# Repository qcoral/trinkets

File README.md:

# trinkets
Misc electronic trinkets &amp; designs I've made!

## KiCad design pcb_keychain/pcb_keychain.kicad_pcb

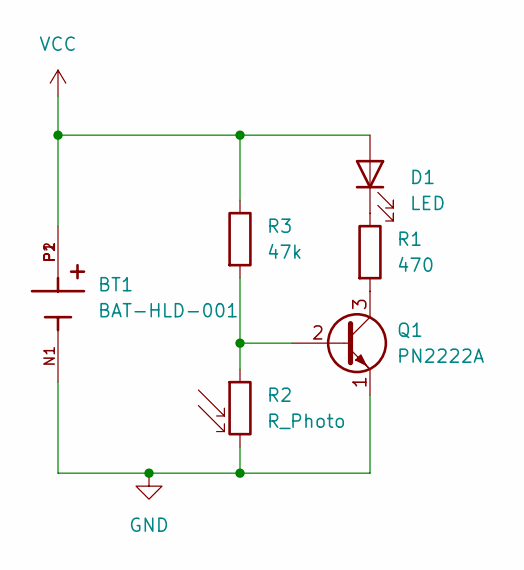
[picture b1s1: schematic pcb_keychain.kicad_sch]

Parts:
BT1: BAT-HLD-001; BAT_BAT-HLD-001; PARTREV C
D1: LED; LED_D8.0mm
Q1: PN2222A; TO-92_Inline
R1: 470; R_Axial_DIN0207_L6.3mm_D2.5mm_P10.16mm_Horizontal
R2: R_Photo; R_LDR_5.1x4.3mm_P3.4mm_Vertical
R3: 47k; R_Axial_DIN0207_L6.3mm_D2.5mm_P10.16mm_Horizontal

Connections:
GND: BT1.N1, Q1.1 (E), R2.2
unnamed: D1.1 (K), R1.1
unnamed: Q1.2 (B), R2.1, R3.2
unnamed: Q1.3 (C), R1.2
VCC: BT1.P1, BT1.P2, D1.2 (A), R3.1

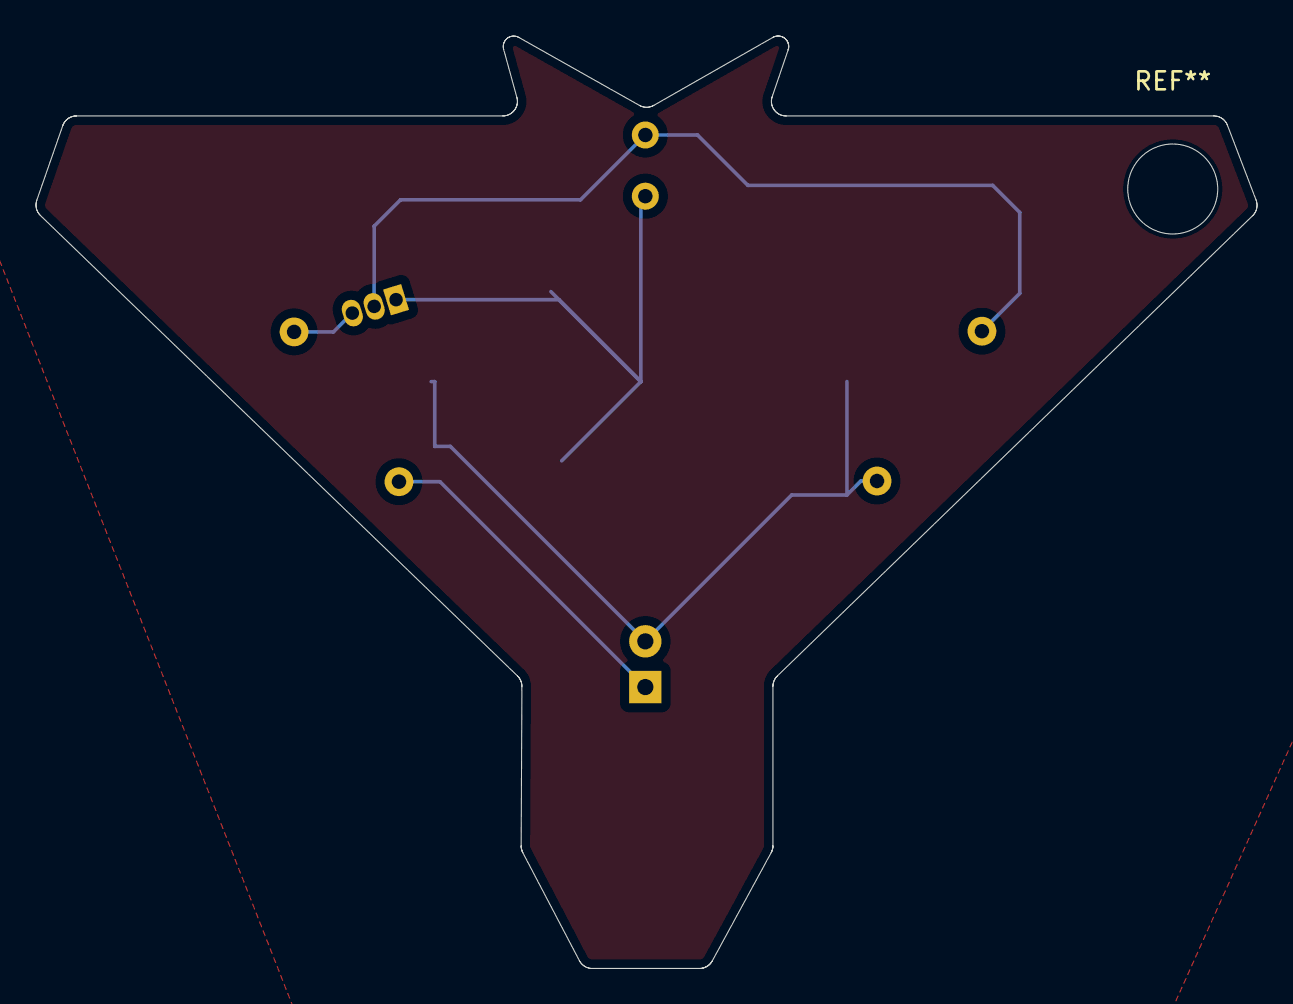
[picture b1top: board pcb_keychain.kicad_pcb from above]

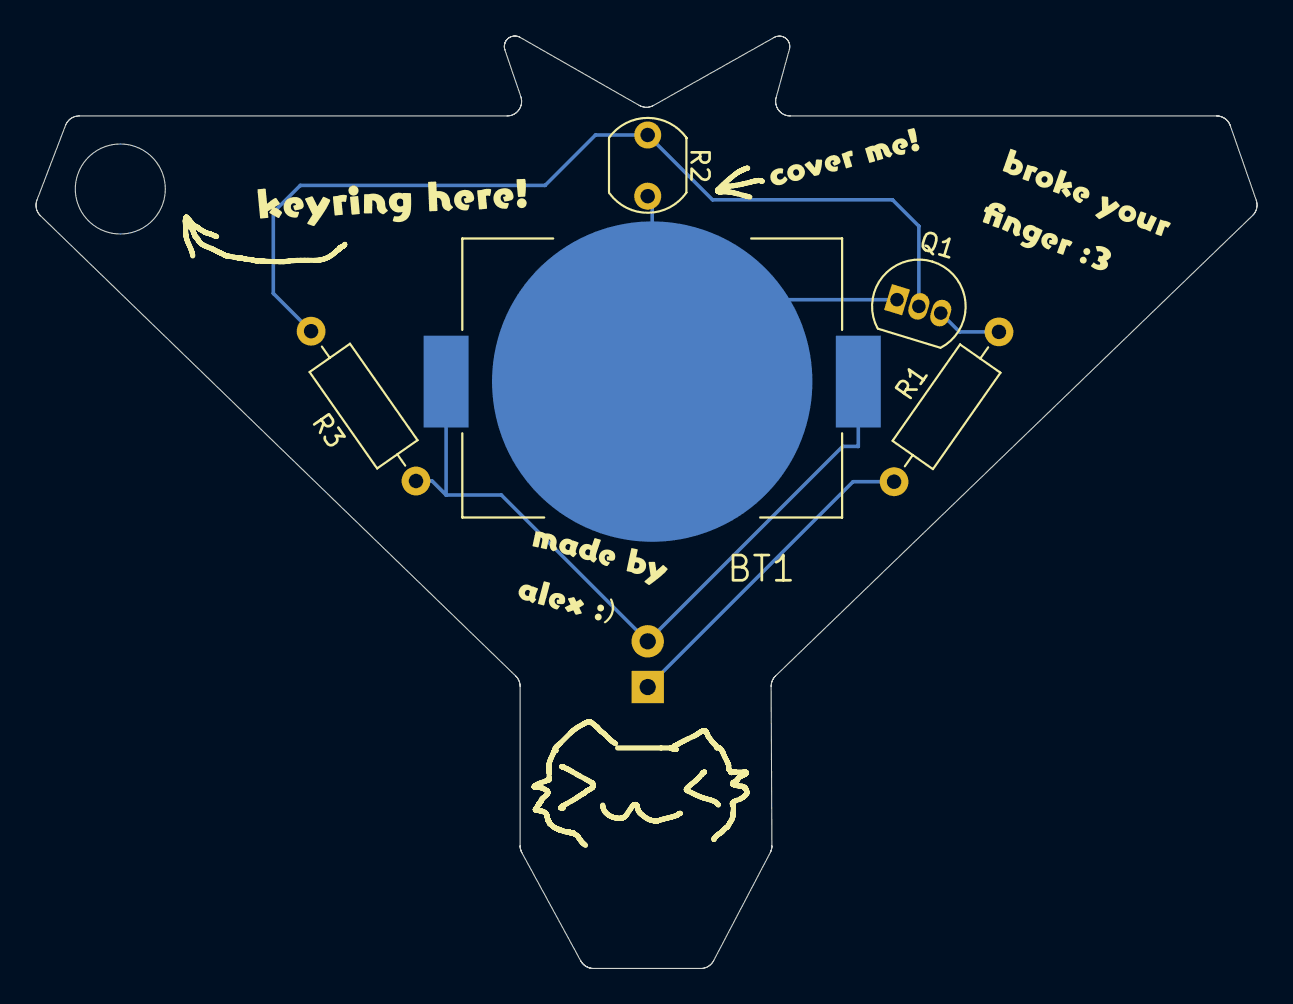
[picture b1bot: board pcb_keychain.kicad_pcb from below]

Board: 11 copper layers, 67.8 x 51.8 mm, 6 parts (5 on the bottom side), 5 nets.

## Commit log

2024-09-29 added initial project
2024-09-30 updated schematic
2024-12-21 updated sch
2025-01-27 added gitignore, counterspell stuff, spaceboard
2025-01-28 moved spaceboard
2025-02-21 added bom'
2025-03-27 updated pcb keychain
2025-03-27 v1 done. holy fk that was a sprint lmao
